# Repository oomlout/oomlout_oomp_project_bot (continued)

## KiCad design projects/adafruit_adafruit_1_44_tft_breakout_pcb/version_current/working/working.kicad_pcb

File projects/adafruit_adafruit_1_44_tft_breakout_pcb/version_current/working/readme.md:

# OOMP Project  
## Adafruit-1.44-TFT-Breakout-PCB  by adafruit  
  
oomp key: oomp_projects_flat_adafruit_adafruit_1_44_tft_breakout_pcb  
(snippet of original readme)  
  
-- Adafruit 1.44" TFT LCD Color Display Breakout PCB  
  
<a href="http://www.adafruit.com/products/2088"><br/>  
Click here to purchase one from the Adafruit shop</a>  
  
PCB files for the Adafruit 1.44 TFT Breakout. Format is EagleCAD schematic and board layout  
* https://www.adafruit.com/products/2088  
  
--- Description  
  
This lovely little display breakout is the best way to add a small, colorful and bright display to any project. Since the display uses 4-wire SPI to communicate and has its own pixel-addressable frame buffer, it can be used with every kind of microcontroller. Even a very small one with low memory and few pins available!  
  
The 1.44" display has 128x128 color pixels. Unlike the low cost "Nokia 6110" and similar LCD displays, which are CSTN type and thus have poor color and slow refresh, this display is a true TFT! The TFT driver (ST7735R) can display full 16-bit color using our library code.  
  
The breakout has the TFT display soldered on (it uses a delicate flex-circuit connector) as well as a ultra-low-dropout 3.3V regulator and a 3/5V level shifter so you can use it with 3.3V or 5V power and logic. We also had a little space so we placed a microSD card holder so you can easily load full color bitmaps from a FAT16/FAT32 formatted microSD card. The microSD card is not included.  
  
NEW! As of February 28, 2023 - we've updated this TFT breakout with an EYESPI connector to make cabling easier with an 18-pin FPC. We also used  
  full source readme at [readme_src.md](readme_src.md)  
  
source repo at: [https://github.com/adafruit/Adafruit-1.44-TFT-Breakout-PCB](https://github.com/adafruit/Adafruit-1.44-TFT-Breakout-PCB)  
## Board  

## Schematic  

[schematic pdf](working_schematic.pdf)  
## Images

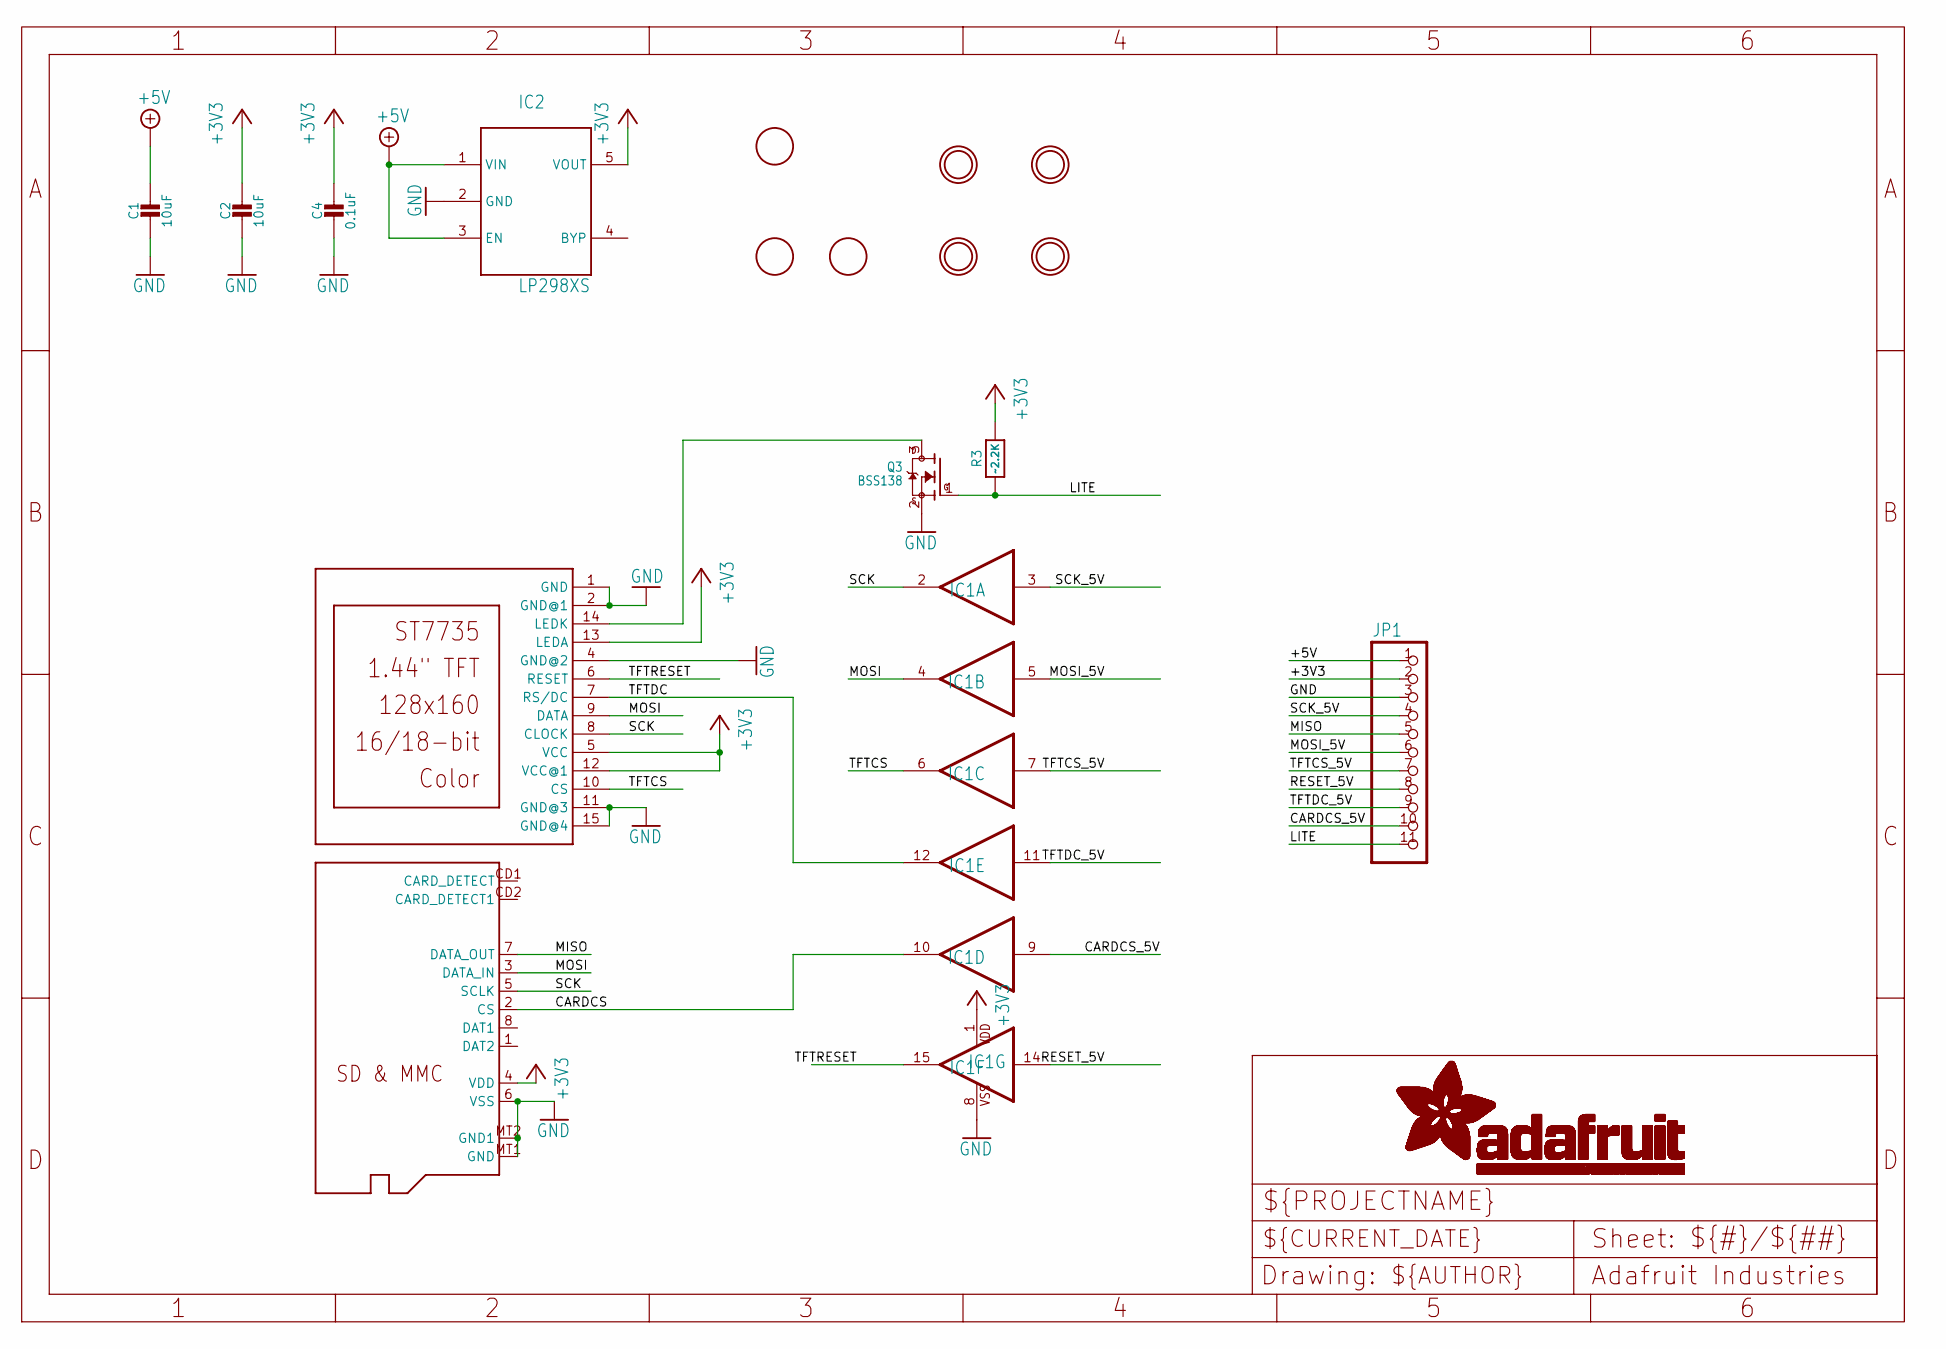
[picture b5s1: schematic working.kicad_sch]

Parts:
C1, C2: 10uF; 0805-NO
C4: 0.1uF; 0805-NO
IC1: 4050D; SO16
IC2: LP298XS; SOT23-5L
JP1: HEADER-1X1176MIL; 1X11_ROUND_76
Q2: MICROSD
Q3: BSS138; SOT23-WIDE
R3: ~2.2K; 0805-NO
TFT2: DISP_LCD_FPC1441609; TFT_FPC1441609
U$3, U$4, U$5: FIDUCIAL; FIDUCIAL_1MM
U$7, U$8, U$9, U$10: MOUNTINGHOLE2.5; MOUNTINGHOLE_2.5_PLATED

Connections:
+3V3: C2.1, C4.1, IC1.1 (VDD), IC2.5 (VOUT), JP1.2, Q2.4 (VDD), R3.2, TFT2.5 (VCC), TFT2.12 (VCC@1), TFT2.13 (LEDA)
+5V: C1.1, IC2.1 (VIN), IC2.3 (EN), JP1.1
CARDCS: IC1.10 (O), Q2.2 (CS)
CARDCS_5V: IC1.9 (I), JP1.10
GND: C1.2, C2.2, C4.2, IC1.8 (VSS), IC2.2 (GND), JP1.3, Q2.6 (VSS), Q2.MT1 (GND), Q2.MT2 (GND1), Q3.2 (S), TFT2.1 (GND), TFT2.2 (GND@1), TFT2.4 (GND@2), TFT2.11 (GND@3), TFT2.15 (GND@4)
LITE: JP1.11, Q3.1 (G), R3.1
MISO: JP1.5, Q2.7 (DATA_OUT)
MOSI: IC1.4 (O), Q2.3 (DATA_IN), TFT2.9 (DATA)
MOSI_5V: IC1.5 (I), JP1.6
unnamed: Q3.3 (D), TFT2.14 (LEDK)
RESET_5V: IC1.14 (I), JP1.8
SCK: IC1.2 (O), Q2.5 (SCLK), TFT2.8 (CLOCK)
SCK_5V: IC1.3 (I), JP1.4
TFTCS: IC1.6 (O), TFT2.10 (CS)
TFTCS_5V: IC1.7 (I), JP1.7
TFTDC: IC1.12 (O), TFT2.7 (RS/DC)
TFTDC_5V: IC1.11 (I), JP1.9
TFTRESET: IC1.15 (O), TFT2.6 (RESET)

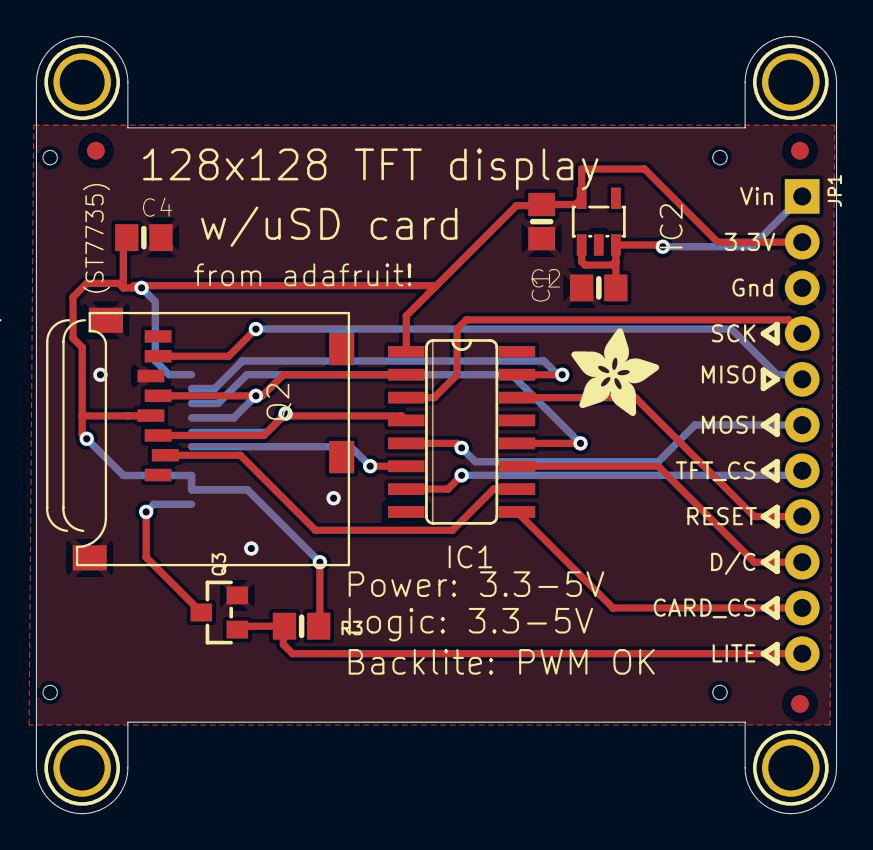
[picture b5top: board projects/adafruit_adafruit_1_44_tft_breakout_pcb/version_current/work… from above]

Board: 16 copper layers, 44.5 x 43.2 mm, 18 parts (1 on the bottom side), 18 nets.

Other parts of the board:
U$1: ADAFRUIT_5MM

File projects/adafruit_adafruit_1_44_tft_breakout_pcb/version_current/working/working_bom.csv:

Row,Description,Part,References,Value,Footprint,Quantity Per PCB,Status,Datasheet
1,,CAP_CERAMIC0805-NOOUTLINE,C4,0.1uF,0805-NO,1, ,
2,,CAP_CERAMIC0805-NOOUTLINE,C1 C2,10uF,0805-NO,2, ,
3,,4050D,IC1,4050D,SO16,1, ,
4,,LP298XS,IC2,LP298XS,SOT23-5L,1, ,
5,,HEADER-1X1176MIL,JP1,HEADER-1X1176MIL,1X11_ROUND_76,1, ,
6,,MOSFET-NWIDE,Q3,BSS138,SOT23-WIDE,1, ,
7,,MICROSD,Q2,MICROSD,MICROSD,1, ,
8,,RESISTOR0805_NOOUTLINE,R3,~2.2K,0805-NO,1, ,
9,,DISP_LCD_FPC1441609,TFT2,DISP_LCD_FPC1441609,TFT_FPC1441609,1, ,





Project info:
Schematic:,working
Variant:,default
Revision:,
Date:,2023-08-02_17-08-32
KiCad Version:,7.0.6-7.0.6~ubuntu22.04.1
Statistics:
Component Groups:,9
Component Count:,10 (0 SMD/ 0 THT)
Fitted Components:,10 (0 SMD/ 0 THT)
Number of PCBs:,1
Total Components:,10

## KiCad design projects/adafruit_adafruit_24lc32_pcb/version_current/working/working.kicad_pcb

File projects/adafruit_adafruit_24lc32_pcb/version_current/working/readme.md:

# OOMP Project  
## Adafruit-24LC32-PCB  by adafruit  
  
oomp key: oomp_projects_flat_adafruit_adafruit_24lc32_pcb  
(snippet of original readme)  
  
-- Adafruit 24LC32 I2C EEPROM Breakout PCB  
  
<a href="http://www.adafruit.com/products/5146"><br/>  
Click here to purchase one from the Adafruit shop</a>  
  
PCB files for the Adafruit 24LC32 I2C EEPROM Breakout.   
  
Format is EagleCAD schematic and board layout  
* https://www.adafruit.com/product/5146  
  
--- Description  
  
If you want to store calibration values, MAC addresses, non-secure access tokens, or other unique identifiers, EEPROM storage is a great option. EEPROM is long lasting, and doesn't need to be written in pages - a single byte can be written at once (unlike with flash memory!) EEPROM storage persists even when the power goes out, and can be over-written literally one million times.  
  
Some microcontrollers, like the ATmega328, have built in EEPROM, usually around 64 to 1024 bytes of it. But some, especially ARM Cortex's, don't! What then? that's where this petite Adafruit 24LC32 I2C EEPROM Breakout comes in to help! With 32 Kbit (4 KByte) of storage, and handy chainable Stemma QT connectors, it's just the right amount of simple I2C-controllable storage. Since its external to your microcontroller or microcomputer, uploading new flash memory won't wipe the data from this chip.  
  
We use the CAT24C32 (or equivalent) EEPROM, internally organized as 4096 words of 8 bits each. It features a 32 byte page write buffer (if you want to write faster than one byte at a time). Use 2 to 5V power/logic and up to 1 MHz clocked I2C. The defa  
  full source readme at [readme_src.md](readme_src.md)  
  
source repo at: [https://github.com/adafruit/Adafruit-24LC32-PCB](https://github.com/adafruit/Adafruit-24LC32-PCB)  
## Board  

## Schematic  

[schematic pdf](working_schematic.pdf)  
## Images

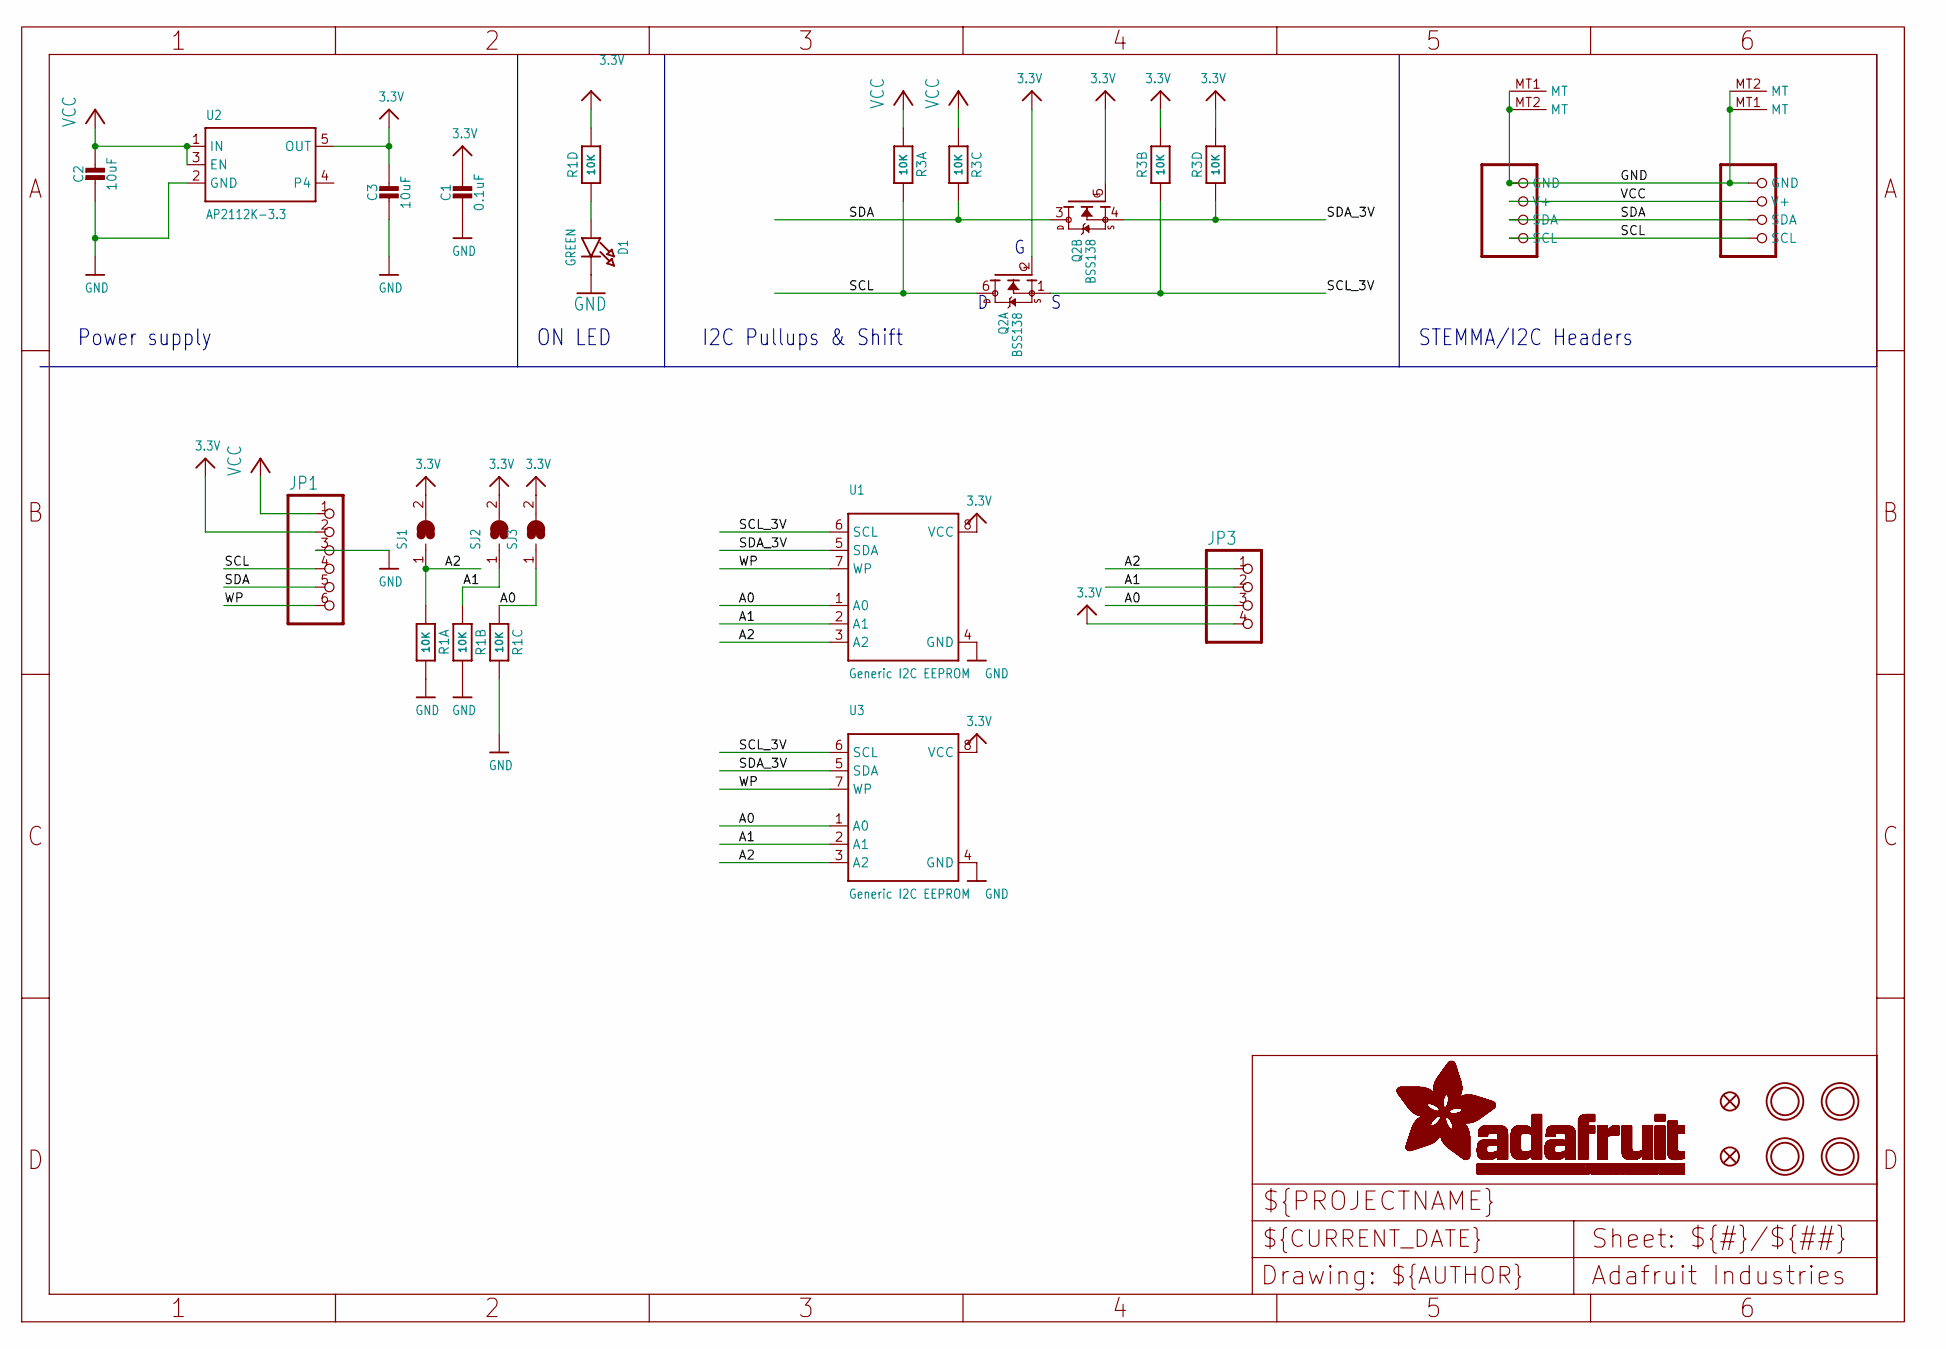
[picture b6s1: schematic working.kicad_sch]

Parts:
C1: 0.1uF; 0603-NO
C2, C3: 10uF; 0805-NO
CONN3, CONN4: STEMMA_I2C_QT; JST_SH4
D1: GREEN; CHIPLED_0603_NOOUTLINE
FID3, FID4: FIDUCIAL_1MM
JP1: HEADER-1X670MIL; 1X06_ROUND_70
JP3: HEADER-1X4ROUND; 1X04_ROUND
Q2: BSS138; SOT363
R1, R3: 10K; RESPACK_4X0603
SJ1, SJ2, SJ3: SOLDERJUMPER; SOLDERJUMPER_ARROW_NOPASTE
U1: Generic I2C EEPROM; SOIC8_150MIL
U2: AP2112K-3.3; SOT23-5
U3: Generic I2C EEPROM; USON8
U$1, U$17, U$19, U$21: MOUNTINGHOLE2.5; MOUNTINGHOLE_2.5_PLATED

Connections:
3.3V: C1.1, C3.1, JP1.2, JP3.4, Q2.2 (G), Q2.5 (G), R1.5 (2), R3.2 (1), R3.4 (1), SJ1.2, SJ2.2, SJ3.2, U1.8 (VCC), U2.5 (OUT), U3.8 (VCC)
A0: JP3.3, R1.3 (1), SJ3.1, U1.1 (A0), U3.1 (A0)
A1: JP3.2, R1.2 (1), SJ2.1, U1.2 (A1), U3.2 (A1)
A2: JP3.1, R1.1, SJ1.1, U1.3 (A2), U3.3 (A2)
GND: C1.2, C2.2, C3.2, CONN3.1 (GND), CONN3.MT1 (MT), CONN3.MT2 (MT), CONN4.1 (GND), CONN4.MT1 (MT), CONN4.MT2 (MT), D1.C, JP1.3, R1.6 (2), R1.7 (2), R1.8 (2), U1.4 (GND), U2.2 (GND), U3.4 (GND)
unnamed: D1.A, R1.4 (1)
SCL: CONN3.4 (SCL), CONN4.4 (SCL), JP1.4, Q2.6 (D), R3.8 (2)
SCL_3V: Q2.1 (S), R3.7 (2), U1.6 (SCL), U3.6 (SCL)
SDA: CONN3.3 (SDA), CONN4.3 (SDA), JP1.5, Q2.3 (D), R3.6 (2)
SDA_3V: Q2.4 (S), R3.5 (2), U1.5 (SDA), U3.5 (SDA)
VCC: C2.1, CONN3.2 (V+), CONN4.2 (V+), JP1.1, R3.1, R3.3 (1), U2.1 (IN), U2.3 (EN)
WP: JP1.6, U1.7 (WP), U3.7 (WP)

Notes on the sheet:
I2C Pullups & Shift
Power supply
ON LED
STEMMA/I2C Headers

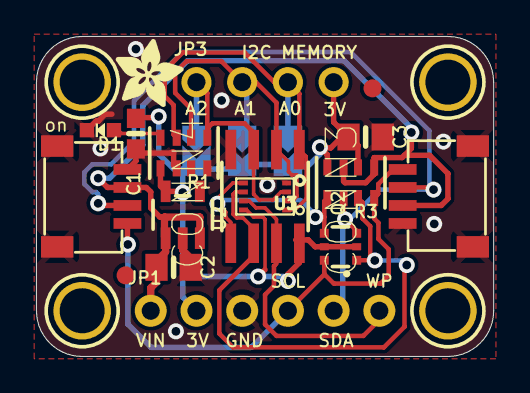
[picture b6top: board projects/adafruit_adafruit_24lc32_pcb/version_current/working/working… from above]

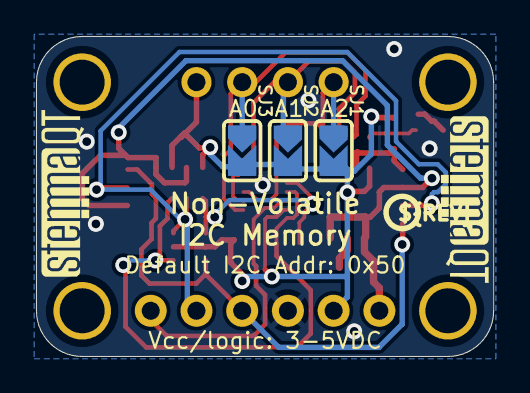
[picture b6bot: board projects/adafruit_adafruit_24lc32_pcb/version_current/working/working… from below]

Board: 2 copper layers, 25.4 x 17.8 mm, 27 parts (6 on the bottom side), 12 nets.

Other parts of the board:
U$25: PCBFEAT-REV-040
U$30, U$31: STEMMAQT
U$32: ADAFRUIT_3.5MM

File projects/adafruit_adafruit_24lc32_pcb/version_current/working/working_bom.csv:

Row,Description,Part,References,Value,Footprint,Quantity Per PCB,Status,Datasheet
1,,CAP_CERAMIC0603_NO,C1,0.1uF,0603-NO,1, ,
2,,CAP_CERAMIC0805-NOOUTLINE,C2 C3,10uF,0805-NO,2, ,
3,,STEMMA_I2C_QT,CONN3 CONN4,STEMMA_I2C_QT,JST_SH4,2, ,
4,,LED0603_NOOUTLINE,D1,GREEN,CHIPLED_0603_NOOUTLINE,1, ,
5,,HEADER-1X4ROUND,JP3,HEADER-1X4ROUND,1X04_ROUND,1, ,
6,,HEADER-1X670MIL,JP1,HEADER-1X670MIL,1X06_ROUND_70,1, ,
7,,MOSFET-N_DUAL,Q2,BSS138,SOT363,1, ,
8,,RESISTOR_4PACK,R1 R3,10K,RESPACK_4X0603,2, ,
9,,VREG_SOT23-5,U2,AP2112K-3.3,SOT23-5,1, ,
10,,EEPROM_I2C_8PIN_GENERIC,U1,Generic I2C EEPROM,SOIC8_150MIL,1, ,
11,,EEPROM_I2C_8PIN_GENERIC_SON8,U3,Generic I2C EEPROM,USON8,1, ,





Project info:
Schematic:,working
Variant:,default
Revision:,
Date:,2023-08-02_17-08-32
KiCad Version:,7.0.6-7.0.6~ubuntu22.04.1
Statistics:
Component Groups:,11
Component Count:,14 (0 SMD/ 0 THT)
Fitted Components:,14 (0 SMD/ 0 THT)
Number of PCBs:,1
Total Components:,14

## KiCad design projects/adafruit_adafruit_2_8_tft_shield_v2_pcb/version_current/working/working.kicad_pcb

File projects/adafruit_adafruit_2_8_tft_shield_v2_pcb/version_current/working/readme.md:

# OOMP Project  
## Adafruit-2.8-TFT-Shield-v2-PCB  by adafruit  
  
oomp key: oomp_projects_flat_adafruit_adafruit_2_8_tft_shield_v2_pcb  
(snippet of original readme)  
  
- Adafruit 2.8 TFT LCD Display Shield v2 PCBs  
&nbsp;   
<br />  
Click to view/purchase from the Adafruit Shop:  
- [2.8" TFT Touch Shield for Arduino with Resistive Touch Screen](https://www.adafruit.com/product/1651)  
- [2.8" TFT Touch Shield for Arduino w/Capacitive Touch](https://www.adafruit.com/product/1947)  
  
Spice up your Arduino project with a beautiful large touchscreen display shield with built in microSD card connection. This TFT display is big (2.8" diagonal) bright (4 white-LED backlight) and colorful (18-bit 262,000 different shades)! 240x320 pixels with individual pixel control. It has way more resolution than a black and white 128x64 display. As a bonus, these displays has a resistive or capacitive touchscreen attached to it already, so you can detect finger presses anywhere on the screen.   
  
We've updated our original v1 shield to an SPI display - its a tiny bit slower but uses a lot less pins and is now much easier to use with Mega & Leonardo. We also include an SPI touchscreen controller so you only need one additional pin to add a high quality touchscreen controller. Even with all the extras, the price is lower thanks to our parts sourcing & engineering skillz!  
  
This is the PCB for the two Adafruit 2.8" TFT Shields v2 Resistive and Capacitive touch screens.   
  
The   
  full source readme at [readme_src.md](readme_src.md)  
  
source repo at: [https://github.com/adafruit/Adafruit-2.8-TFT-Shield-v2-PCB](https://github.com/adafruit/Adafruit-2.8-TFT-Shield-v2-PCB)  
## Board  

## Schematic  

[schematic pdf](working_schematic.pdf)  
## Images

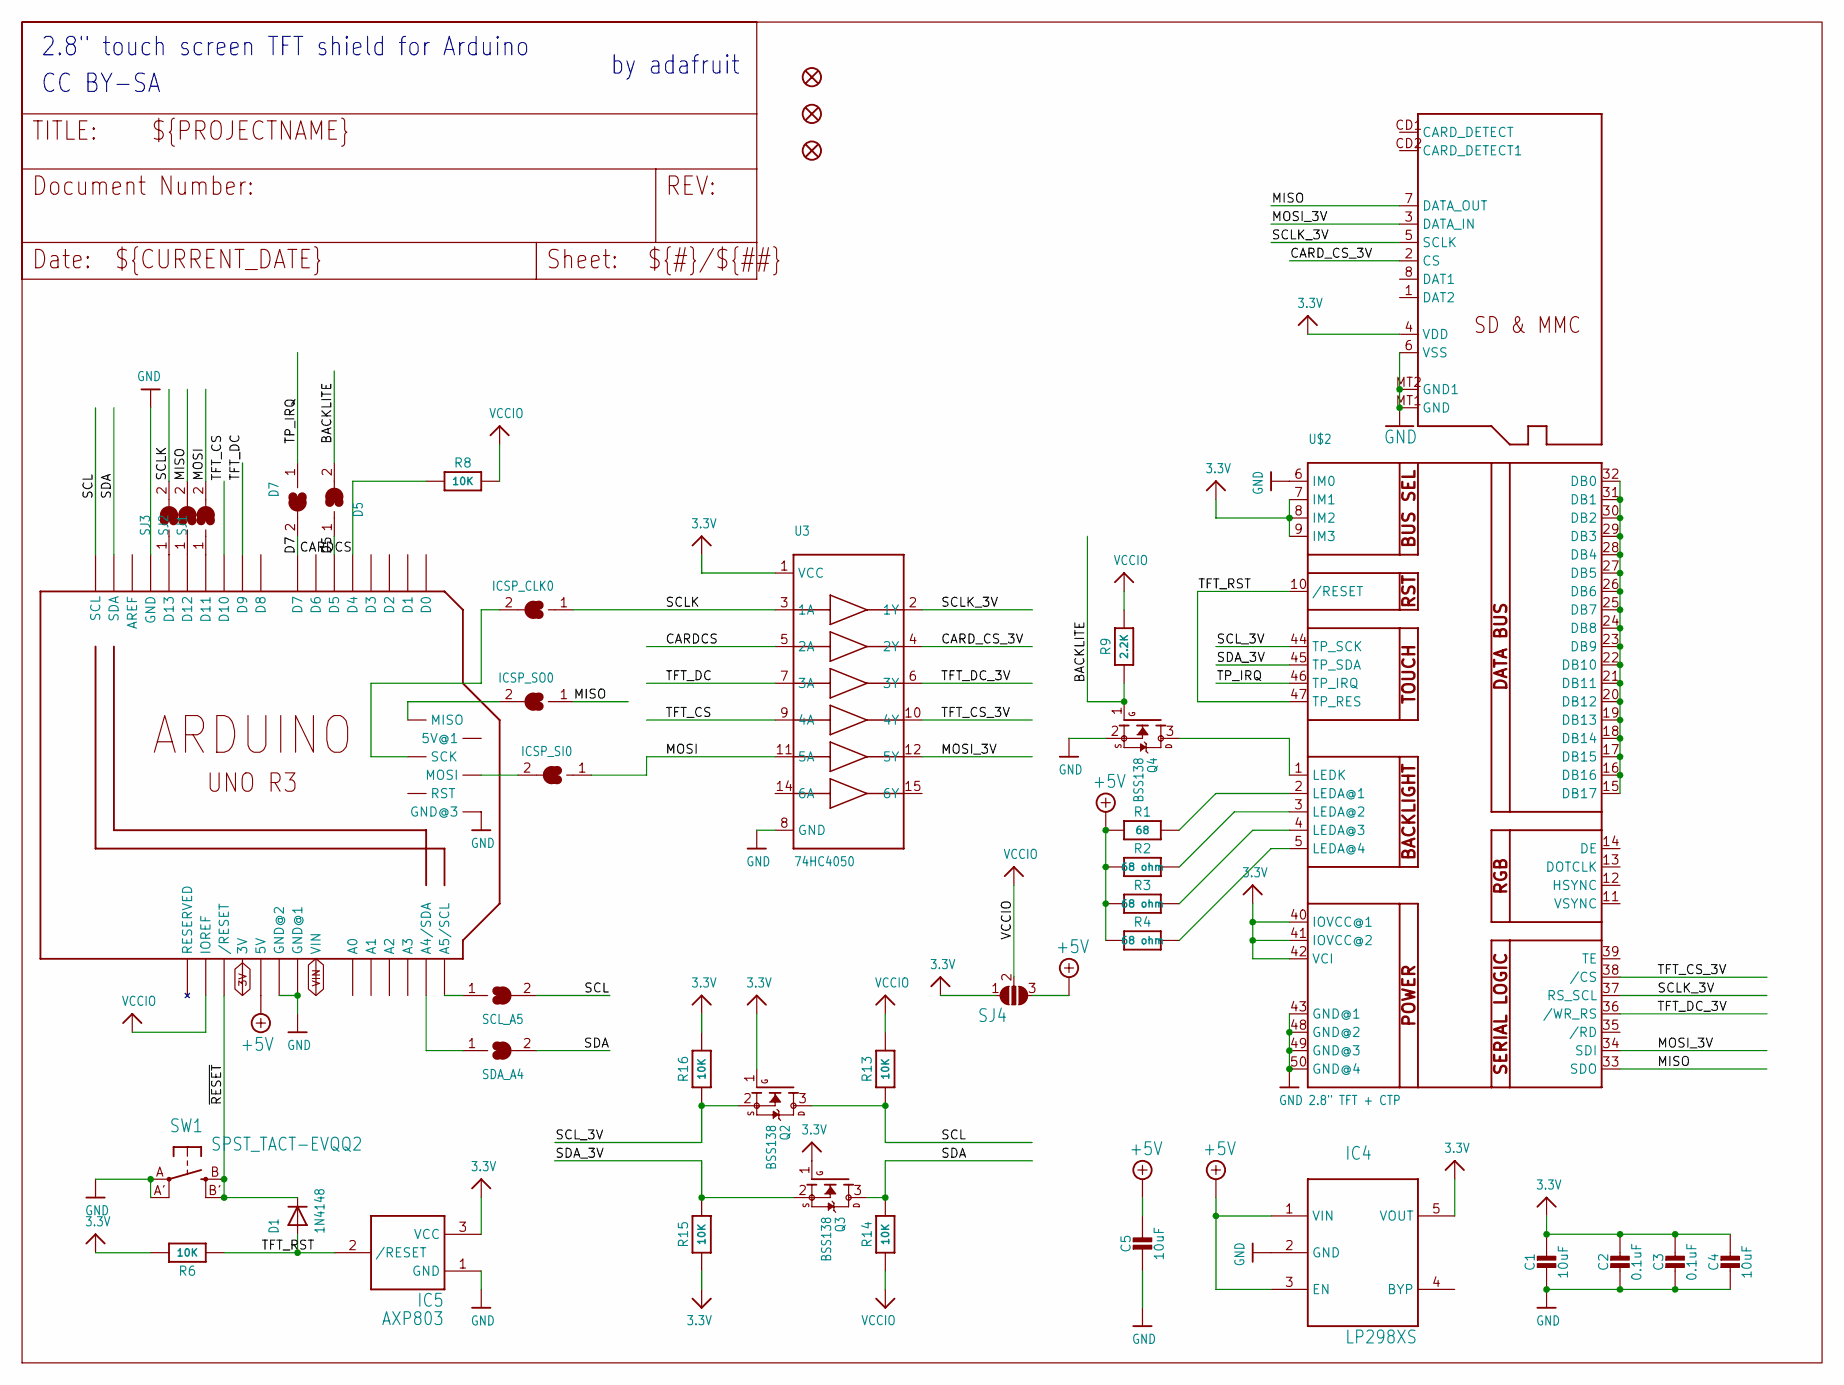
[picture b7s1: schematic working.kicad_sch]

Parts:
C1, C4, C5: 10uF; 0805-NO
C2, C3: 0.1uF; 0805-NO
D1: 1N4148; SOD-323F
D5, D7: SOLDERJUMPER; SOLDERJUMPER_ARROW_NOPASTE
IC4: LP298XS; SOT23-5L
IC5: AXP803; SOT23
ICSP_CLK0: SOLDERJUMPERCLOSED; SOLDERJUMPER_CLOSEDWIRE
ICSP_SI0: SOLDERJUMPERCLOSED; SOLDERJUMPER_CLOSEDWIRE
ICSP_SO0: SOLDERJUMPERCLOSED; SOLDERJUMPER_CLOSEDWIRE
Q2, Q3, Q4: BSS138; SOT23-WIDE
R1: 68; 0805-NO
R2, R3, R4: 68 ohm; 0805-NO
R6, R8, R13, R14, R15, R16: 10K; 0805-NO
R9: 2.2K; 0805-NO
SCL_A5: SOLDERJUMPERREFLOW_NOPASTE; SOLDERJUMPER_REFLOW_NOPASTE
SDA_A4: SOLDERJUMPERREFLOW_NOPASTE; SOLDERJUMPER_REFLOW_NOPASTE
SJ1, SJ2, SJ3: SOLDERJUMPER; SOLDERJUMPER_ARROW_NOPASTE
SJ4: SOLDERJUMPER_2WAY; SOLDERJUMPER_2WAY_OPEN_NOPASTE
SW1: SPST_TACT-EVQQ2; EVQ-Q2
U3: 74HC4050; SOIC16
U$2: 2.8" TFT + CTP; TFT_2.83IN_240X320_50PIN
U$3: MICROSD
U$10, U$11, U$19: FIDUCIAL_1MM
U$17: ARDUINO_R3_ICSPSMT; ARDUINOR3_ICSP_SMT

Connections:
3.3V: C1.1, C2.1, C3.1, C4.1, IC4.5 (VOUT), IC5.3 (VCC), Q2.1 (G), Q3.1 (G), R6.2, R15.1, R16.2, SJ4.1, U3.1 (VCC), U$2.7 (IM1), U$2.8 (IM2), U$2.9 (IM3), U$2.40 (IOVCC@1), U$2.41 (IOVCC@2), U$2.42 (VCI), U$3.4 (VDD)
3V: U$17.3V
+5V: C5.1, IC4.1 (VIN), IC4.3 (EN), R1.1, R2.1, R3.1, R4.1, SJ4.3, U$17.5V
BACKLITE: D5.2, Q4.1 (G), R9.1
CARDCS: R8.1, U3.5 (2A), U$17.D4
CARD_CS_3V: U3.4 (2Y), U$3.2 (CS)
D5: D5.1, U$17.D5
D7: D7.2, U$17.D7
GND: C1.2, C2.2, C3.2, C4.2, C5.2, IC4.2 (GND), IC5.1 (GND), Q4.2 (S), SW1.A, SW1.A' (P1), U3.8 (GND), U$2.6 (IM0), U$2.43 (GND@1), U$2.48 (GND@2), U$2.49 (GND@3), U$2.50 (GND@4), U$3.6 (VSS), U$3.MT1 (GND), U$3.MT2 (GND1), U$17.GND, U$17.GND@1, U$17.GND@2, U$17.GND@3
MISO: ICSP_SO0.1, SJ2.2, U$2.33 (SDO), U$3.7 (DATA_OUT)
MOSI: ICSP_SI0.1, SJ1.2, U3.11 (5A)
MOSI_3V: U3.12 (5Y), U$2.34 (SDI), U$3.3 (DATA_IN)
unnamed: Q4.3 (D), U$2.1 (LEDK)
unnamed: R1.2, U$2.2 (LEDA@1)
unnamed: R2.2, U$2.3 (LEDA@2)
unnamed: R3.2, U$2.4 (LEDA@3)
unnamed: ICSP_SI0.2, U$17.MOSI
unnamed: U$2.15 (DB17), U$2.16 (DB16), U$2.17 (DB15), U$2.18 (DB14), U$2.19 (DB13), U$2.20 (DB12), U$2.21 (DB11), U$2.22 (DB10), U$2.23 (DB9), U$2.24 (DB8), U$2.25 (DB7), U$2.26 (DB6), U$2.27 (DB5), U$2.28 (DB4), U$2.29 (DB3), U$2.30 (DB2), U$2.31 (DB1), U$2.32 (DB0)
unnamed: R4.2, U$2.5 (LEDA@4)
unnamed: ICSP_SO0.2, U$17.MISO
unnamed: ICSP_CLK0.2, U$17.SCK
unnamed: SJ3.1, U$17.D13
unnamed: SJ2.1, U$17.D12
unnamed: SJ1.1, U$17.D11
unnamed: SDA_A4.1, U$17.A4 (A4/SDA)
unnamed: SCL_A5.1, U$17.A5 (A5/SCL)
SCL: Q2.3 (D), R13.1, SCL_A5.2, U$17.SCL
SCLK: ICSP_CLK0.1, SJ3.2, U3.3 (1A)
SCLK_3V: U3.2 (1Y), U$2.37 (RS_SCL), U$3.5 (SCLK)
SCL_3V: Q2.2 (S), R16.1, U$2.44 (TP_SCK)
SDA: Q3.3 (D), R14.2, SDA_A4.2, U$17.SDA
SDA_3V: Q3.2 (S), R15.2, U$2.45 (TP_SDA)
TFT_CS: U3.9 (4A), U$17.D10
TFT_CS_3V: U3.10 (4Y), U$2.38 (/CS)
TFT_DC: U3.7 (3A), U$17.D9
TFT_DC_3V: U3.6 (3Y), U$2.36 (/WR_RS)
TFT_RST: D1.A, IC5.2 (/RESET), R6.1, U$2.10 (/RESET), U$2.47 (TP_RES)
TP_IRQ: D7.1, U$2.46 (TP_IRQ)
VCCIO: R8.2, R9.2, R13.2, R14.1, SJ4.2, U$17.IOREF
VIN: U$17.VIN
~RESET: D1.C, SW1.B (S), SW1.B' (S1), U$17.RESET (/RESET)

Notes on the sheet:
CC BY-SA
by adafruit~{}
2.8" touch screen TFT shield for Arduino

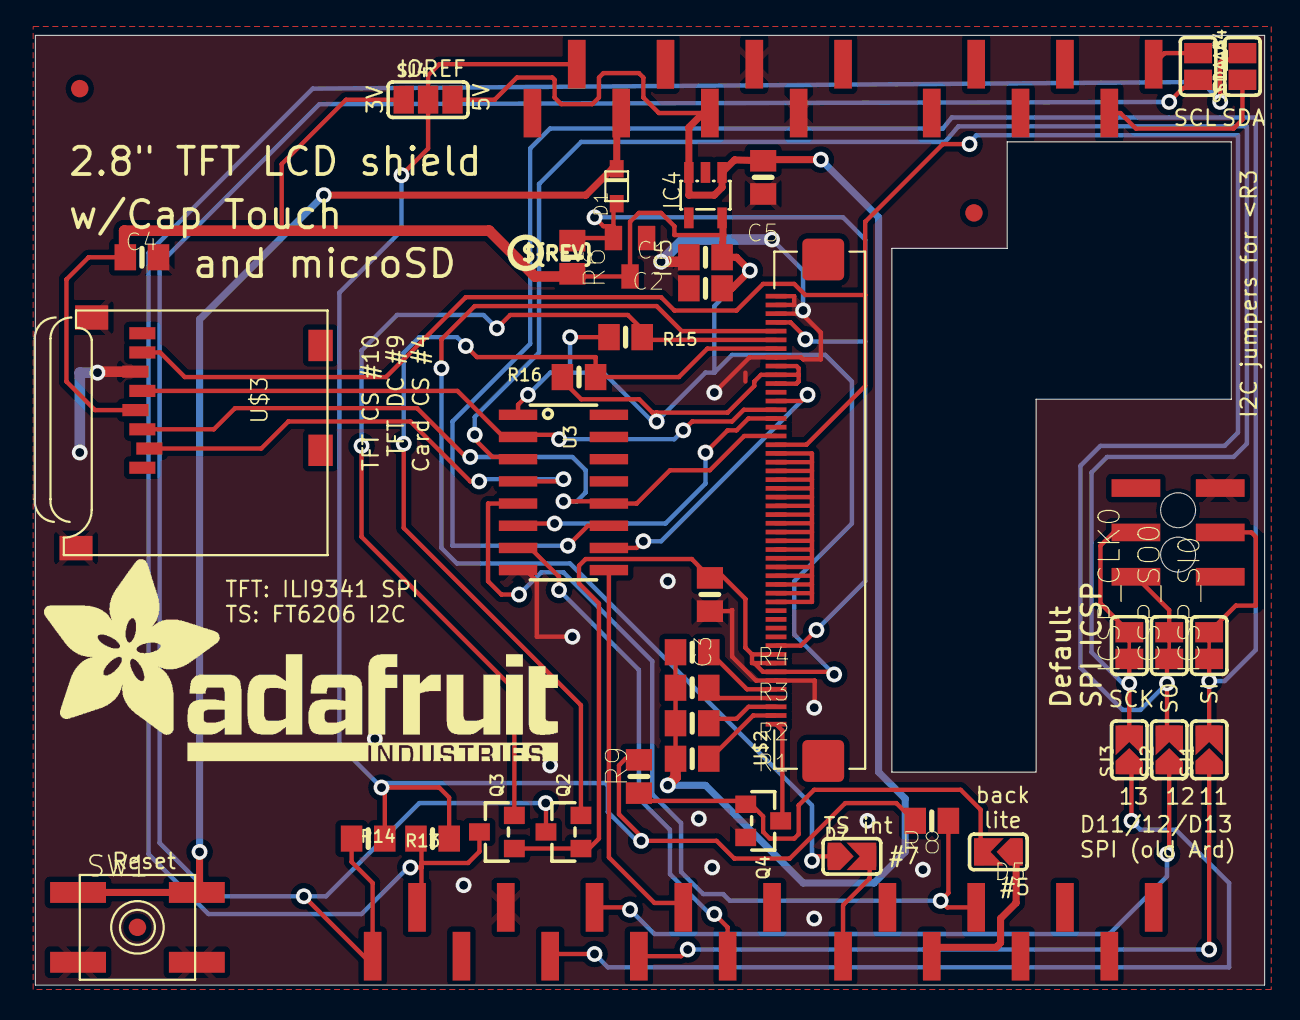
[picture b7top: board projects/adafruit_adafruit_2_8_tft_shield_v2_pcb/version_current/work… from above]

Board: 16 copper layers, 70.4 x 54.4 mm, 43 parts (2 on the bottom side), 39 nets.

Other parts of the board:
U$7: PCBFEAT-REV-040
U$20: ADAFRUIT_TEXT_30MM

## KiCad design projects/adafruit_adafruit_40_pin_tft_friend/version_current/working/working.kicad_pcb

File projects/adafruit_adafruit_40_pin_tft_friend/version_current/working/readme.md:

# OOMP Project  
## Adafruit-40-pin-TFT-Friend  by adafruit  
  
oomp key: oomp_projects_flat_adafruit_adafruit_40_pin_tft_friend  
(snippet of original readme)  
  
-- Adafruit-40-pin-TFT-Friend  
  
<a href="http://www.adafruit.com/products/1932"><br/>  
Click here to purchase one from the Adafruit shop</a>  
  
These are the Eagle CAD files for the Adafruit 40-pin TFT Friend / Breakout Board  
- https://www.adafruit.com/product/1932  
  
This breakout board is something we designed in-house to help us work with 'dot-clock' 40-pin TFT displays that require the RGB pixel data to be clocked in continuously. These displays have 40-pin Flex PCB (FPC) cables and often require a boost converter for the backlight LED, which makes them annoying to breadboard. To make them breadboardable, we stuck a 40-pin FPC and a FAN5333-based backlight driver with adjustable current onto a labeled breakout board. Now you can poke and probe each pin!  
  
The backlight driver defaults to 25mA and can boost up to 24VDC for up to 7-LED strings. Check your display datasheet for the string configuration, and short out the jumpers to increase the backlight current.   
  
--- License  
  
Adafruit invests time and resources providing this open source design, please support Adafruit and open-source hardware by purchasing products from [Adafruit.com](https://www.adafruit.com)!  
  
Creative Commons Attribution, Share-Alike license, check license.txt for more information All text above must be included in any redistribution -   
See license.txt for more information.  
  
  full source readme at [readme_src.md](readme_src.md)  
  
source repo at: [https://github.com/adafruit/Adafruit-40-pin-TFT-Friend](https://github.com/adafruit/Adafruit-40-pin-TFT-Friend)  
## Board  

## Schematic  

[schematic pdf](working_schematic.pdf)  
## Images

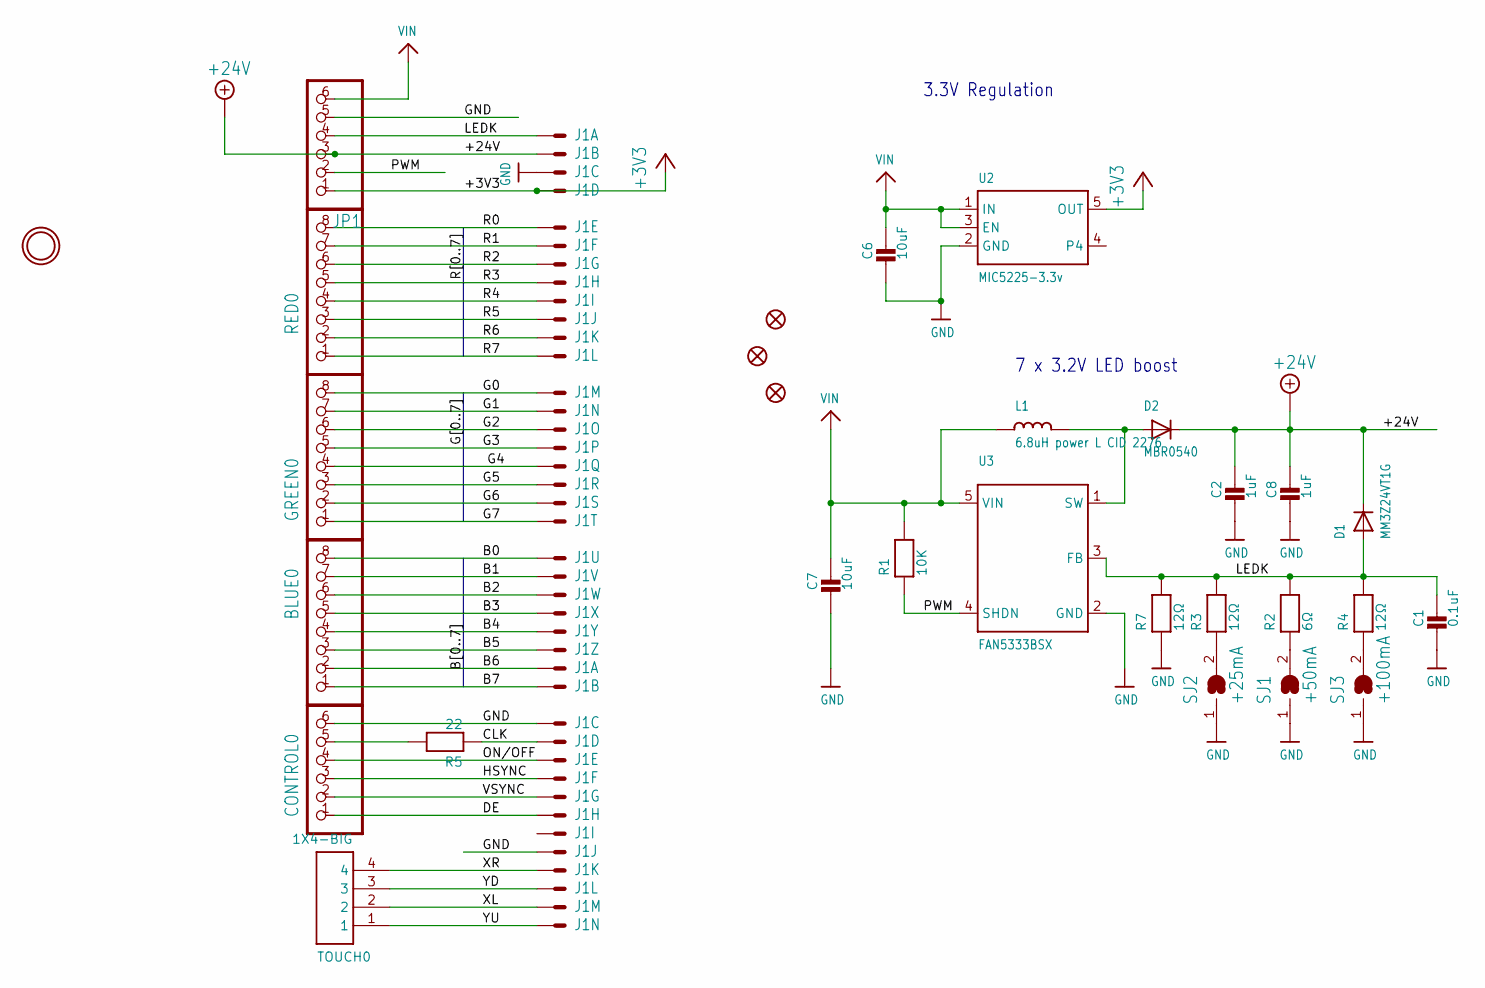
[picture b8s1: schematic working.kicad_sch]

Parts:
BLUE0: PINHD-1X8BIG; 1X08-BIG
C1: 0.1uF; _0805MP
C2, C8: 1uF; _0805MP
C6, C7: 10uF; _0805MP
CONTROL0: PINHD-1X6B; 1X06-BIG
D1: MM3Z24VT1G; SMADIODE
D2: MBR0540; SOD-123
FID1, FID2, FID3: FIDUCIAL""; FIDUCIAL_1MM
GREEN0: PINHD-1X8BIG; 1X08-BIG
J1: 40PINFPC4-1734839-0; 4-1734839-0
JP1: PINHD-1X6B; 1X06-BIG
L1: 6.8uH power L CID 2276; INDUCTOR_5X5MM_NR5040_NOTHERMALS
R1: 10K; _0805MP
R2: 6Ω; _0805MP
R3, R4, R7: 12Ω; _0805MP
R5: 22; _0805MP
RED0: PINHD-1X8BIG; 1X08-BIG
SJ1: +50mA; SOLDERJUMPER_ARROW_NOPASTE
SJ2: +25mA; SOLDERJUMPER_ARROW_NOPASTE
SJ3: +100mA; SOLDERJUMPER_ARROW_NOPASTE
TOUCH0: 1X4-BIG; 1X04-BIG
U2: MIC5225-3.3v; SOT23-5
U3: FAN5333BSX; SOT23-5@1
U$7: MOUNTINGHOLE2.5; MOUNTINGHOLE_2.5_PLATED

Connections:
+3V3: J1.4 (MS), JP1.1, U2.5 (OUT)
+24V: C2.1, C8.1, D1.C, D2.C, J1.2 (MS), JP1.3
B0: BLUE0.8, J1.21 (MS)
B1: BLUE0.7, J1.22 (MS)
B2: BLUE0.6, J1.23 (MS)
B3: BLUE0.5, J1.24 (MS)
B4: BLUE0.4, J1.25 (MS)
B5: BLUE0.3, J1.26 (MS)
B6: BLUE0.2, J1.27 (MS)
B7: BLUE0.1, J1.28 (MS)
CLK: J1.30 (MS), R5.1
DE: CONTROL0.1, J1.34 (MS)
G0: GREEN0.8, J1.13 (MS)
G1: GREEN0.7, J1.14 (MS)
G2: GREEN0.6, J1.15 (MS)
G3: GREEN0.5, J1.16 (MS)
G4: GREEN0.4, J1.17 (MS)
G5: GREEN0.3, J1.18 (MS)
G6: GREEN0.2, J1.19 (MS)
G7: GREEN0.1, J1.20 (MS)
GND: C1.2, C2.2, C6.2, C7.2, C8.2, CONTROL0.6, J1.3 (MS), J1.29 (MS), J1.36 (MS), JP1.5, R7.1, SJ1.1, SJ2.1, SJ3.1, U2.2 (GND), U3.2 (GND)
HSYNC: CONTROL0.3, J1.32 (MS)
LEDK: C1.1, D1.A, J1.1 (MSV), JP1.4, R2.2, R3.2, R4.2, R7.2, U3.3 (FB)
unnamed: R2.1, SJ1.2
unnamed: R3.1, SJ2.2
unnamed: R4.1, SJ3.2
unnamed: CONTROL0.5, R5.2
unnamed: D2.A, L1.P$2 (2), U3.1 (SW)
ON/OFF: CONTROL0.4, J1.31 (MS)
PWM: JP1.2, R1.1, U3.4 (SHDN)
R0: J1.5 (MS), RED0.8
R1: J1.6 (MS), RED0.7
R2: J1.7 (MS), RED0.6
R3: J1.8 (MS), RED0.5
R4: J1.9 (MS), RED0.4
R5: J1.10 (MS), RED0.3
R6: J1.11 (MS), RED0.2
R7: J1.12 (MS), RED0.1
VIN: C6.1, C7.1, JP1.6, L1.P$1 (1), R1.2, U2.1 (IN), U2.3 (EN), U3.5 (VIN)
VSYNC: CONTROL0.2, J1.33 (MS)
XL: J1.39 (MS), TOUCH0.2
XR: J1.37 (MS), TOUCH0.4
YD: J1.38 (MS), TOUCH0.3
YU: J1.40 (MS), TOUCH0.1

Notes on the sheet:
7 x 3.2V LED boost
3.3V Regulation

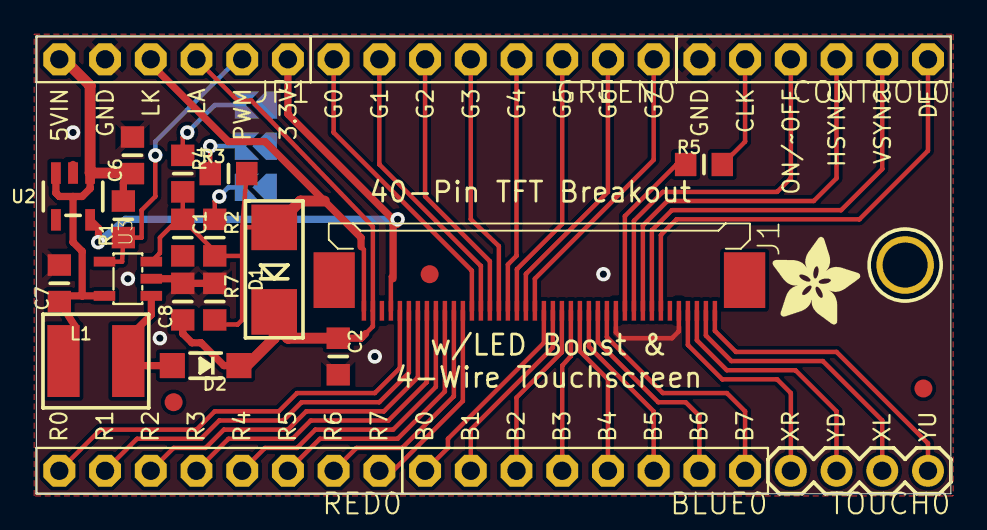
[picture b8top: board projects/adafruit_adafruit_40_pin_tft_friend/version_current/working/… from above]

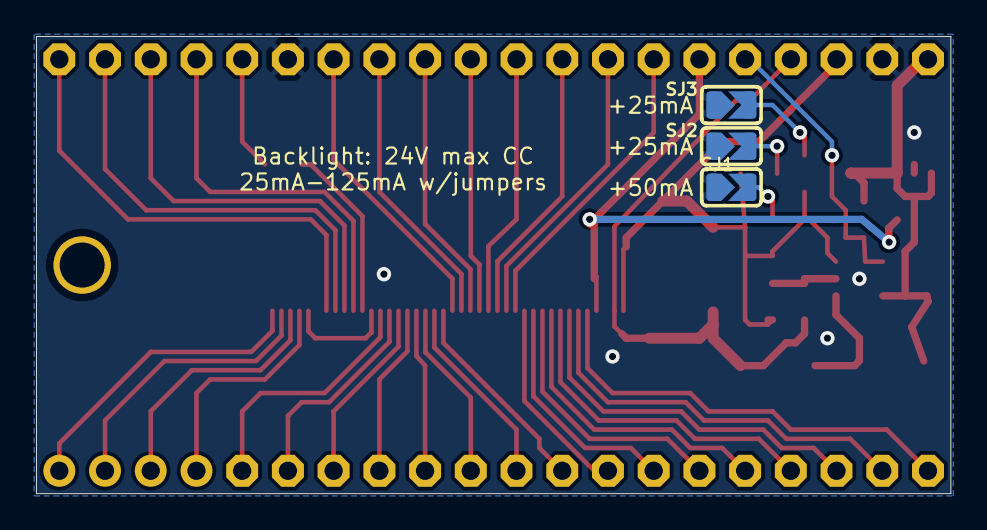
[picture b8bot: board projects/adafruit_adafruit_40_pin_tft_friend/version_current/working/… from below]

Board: 2 copper layers, 50.8 x 25.4 mm, 31 parts (3 on the bottom side), 44 nets.

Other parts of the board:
U$15: ADAFRUIT_5MM
